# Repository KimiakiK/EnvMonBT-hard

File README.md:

# EnvMonBT
[Software](https://github.com/KimiakiK/EnvMonBT-soft)

# Features
- 温度湿度気圧CO2計
- 直近1時間と24時間のグラフ表示
- 統計表示(平均、最大、最小)
- BLE接続

# Major Components  
- STM32F303K8
- 温湿度・気圧センサ BME280
- CO2センサ MH-Z19
- TFT 1.3インチ 240x240ドット
- Bluetooth RN4020

# Photos

## PCB
- V2.1

- V2.0

- V1.0

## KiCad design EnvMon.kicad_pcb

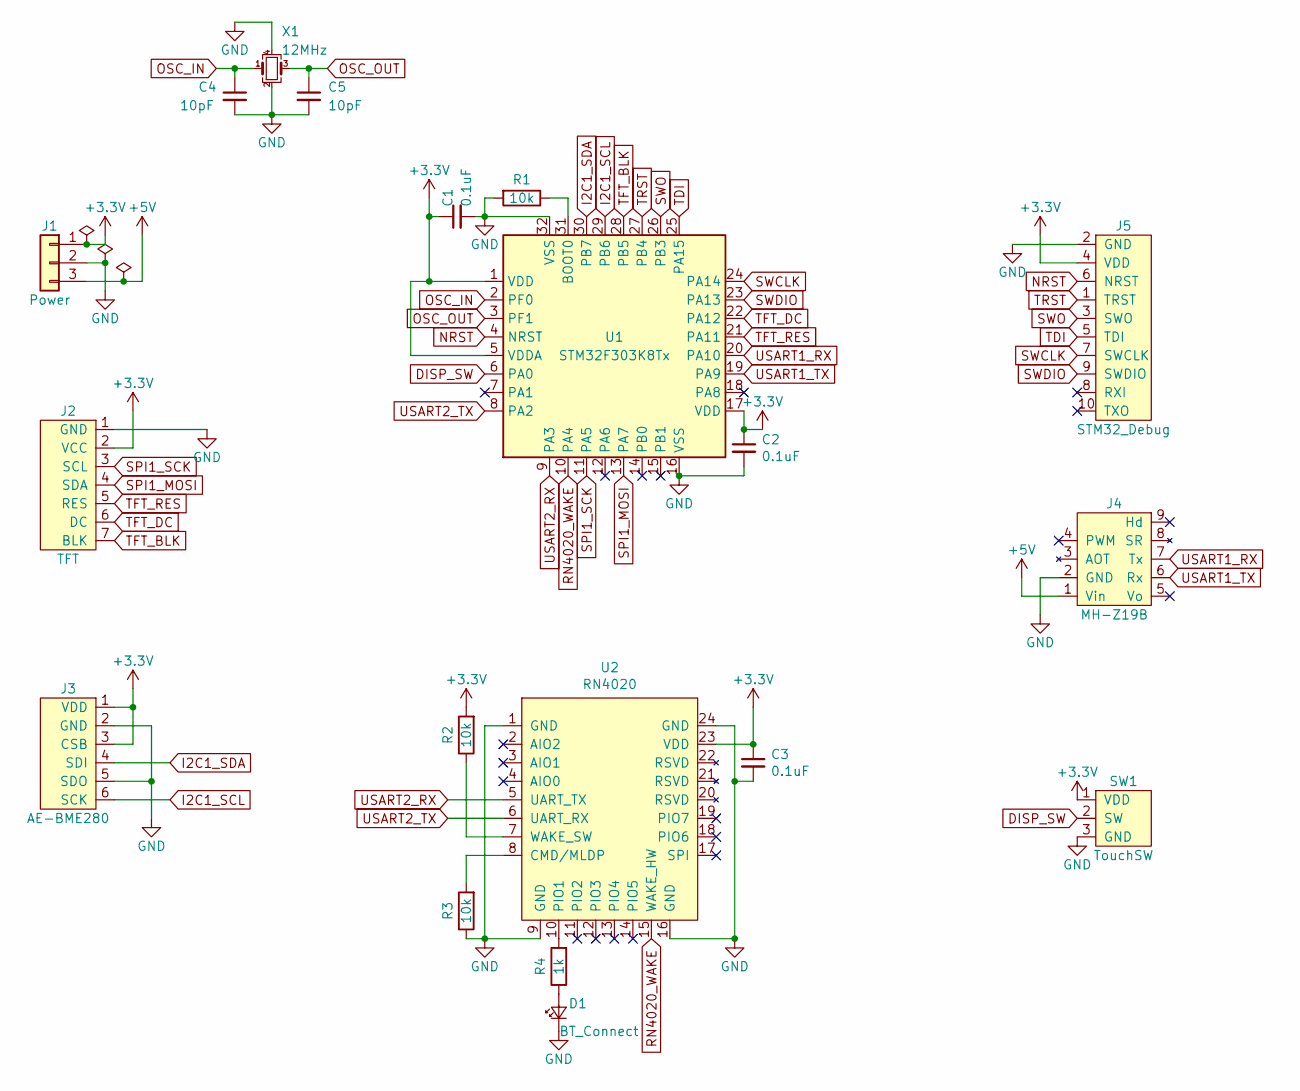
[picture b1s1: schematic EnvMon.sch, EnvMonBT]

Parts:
C1, C2, C3: 0.1uF; C_0603_1608Metric_Pad1.05x0.95mm_HandSolder
C4, C5: 10pF; C_0402_1005Metric
D1: BT_Connect; LED_0603_1608Metric_Pad1.05x0.95mm_HandSolder
J1: Power; USB_Power_Pin
J2: TFT; TFT_1.3_IPA
J3: AE-BME280; PinSocket_1x06_P2.54mm_Vertical
J4: MH-Z19B
J5: STM32_Debug; PinHeader_2x05_P1.27mm_Vertical
R1, R2, R3: 10k; R_0603_1608Metric_Pad1.05x0.95mm_HandSolder
R4: 1k; R_0603_1608Metric_Pad1.05x0.95mm_HandSolder
SW1: TouchSW
U1: STM32F303K8Tx; LQFP-32_7x7mm_P0.8mm_FusionPCB
U2: RN4020
X1: 12MHz; Crystal_SMD_3225-4Pin_3.2x2.5mm_HandSoldering

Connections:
+3V3: C1.1, C2.1, C3.1, J1.1, J2.2 (VCC), J3.1 (VDD), J3.3 (CSB), J5.4 (VDD), R2.2, SW1.1 (VDD), U1.1 (VDD), U1.5 (VDDA), U1.17 (VDD), U2.23 (VDD)
+5V: J1.3, J4.1 (Vin)
DISP_SW: SW1.2 (SW), U1.6 (PA0)
GND: C1.2, C2.2, C3.2, C4.2, C5.2, D1.1 (K), J1.2, J2.1 (GND), J3.2 (GND), J3.5 (SDO), J4.2 (GND), J5.2 (GND), R1.2, R3.1, SW1.3 (GND), U1.16 (VSS), U1.32 (VSS), U2.1 (GND), U2.9 (GND), U2.16 (GND), U2.24 (GND), X1.2, X1.4
I2C1_SCL: J3.6 (SCK), U1.29 (PB6)
I2C1_SDA: J3.4 (SDI), U1.30 (PB7)
NRST: J5.6 (NRST), U1.4 (NRST)
unnamed: D1.2 (A), R4.1
unnamed: R1.1, U1.31 (BOOT0)
unnamed: R2.1, U2.7 (WAKE_SW)
unnamed: R3.2, U2.8 (CMD/MLDP)
unnamed: R4.2, U2.10 (PIO1)
OSC_IN: C4.1, U1.2 (PF0), X1.1
OSC_OUT: C5.1, U1.3 (PF1), X1.3
RN4020_WAKE: U1.10 (PA4), U2.15 (WAKE_HW)
SPI1_MOSI: J2.4 (SDA), U1.13 (PA7)
SPI1_SCK: J2.3 (SCL), U1.11 (PA5)
SWCLK: J5.7 (SWCLK), U1.24 (PA14)
SWDIO: J5.9 (SWDIO), U1.23 (PA13)
SWO: J5.3 (SWO), U1.26 (PB3)
TDI: J5.5 (TDI), U1.25 (PA15)
TFT_BLK: J2.7 (BLK), U1.28 (PB5)
TFT_DC: J2.6 (DC), U1.22 (PA12)
TFT_RES: J2.5 (RES), U1.21 (PA11)
TRST: J5.1 (TRST), U1.27 (PB4)
USART1_RX: J4.7 (Tx), U1.20 (PA10)
USART1_TX: J4.6 (Rx), U1.19 (PA9)
USART2_RX: U1.9 (PA3), U2.5 (UART_TX)
USART2_TX: U1.8 (PA2), U2.6 (UART_RX)

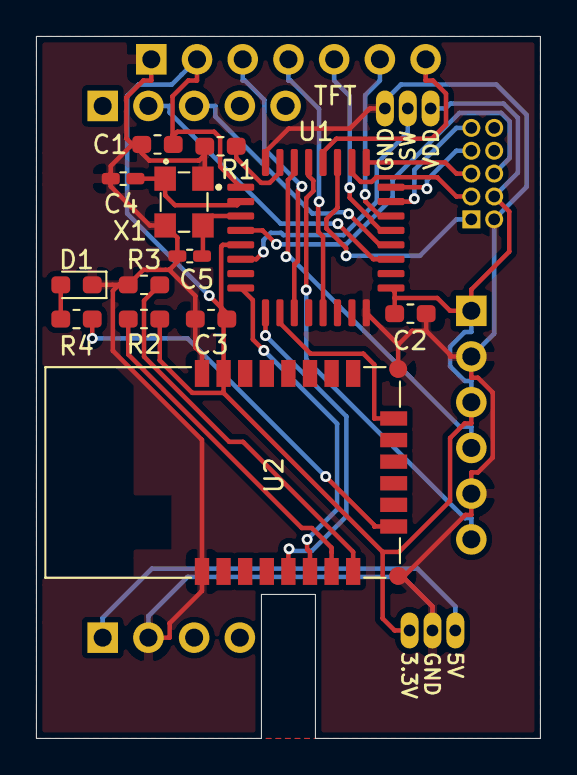
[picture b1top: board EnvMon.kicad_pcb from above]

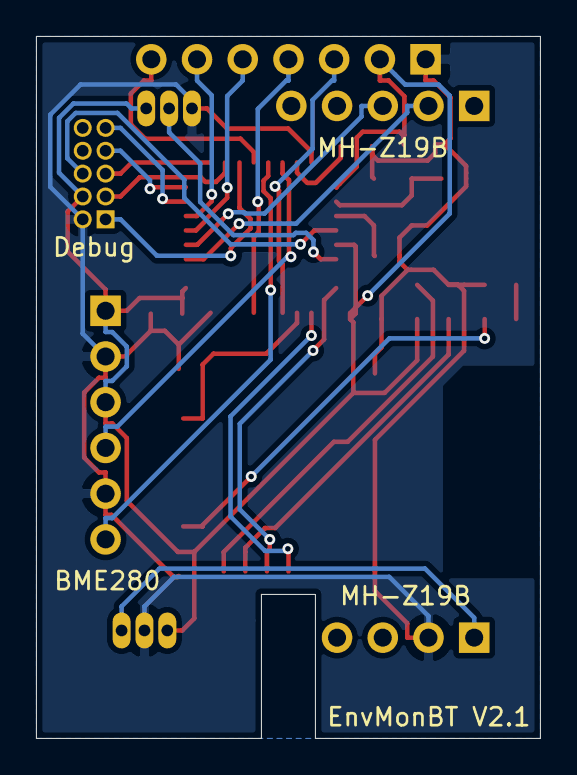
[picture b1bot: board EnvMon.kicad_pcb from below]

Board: 2 copper layers, 28.0 x 39.0 mm, 19 parts (3 on the bottom side), 29 nets.

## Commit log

2021-02-10 基板 V1.0
2021-02-10 基板 V2.0
2021-02-10 基板 V2.1
2021-04-29 Add images
